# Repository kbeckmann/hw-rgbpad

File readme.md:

See [https://dox.xil.se/projects/rgbpad/](https://dox.xil.se/projects/rgbpad/)

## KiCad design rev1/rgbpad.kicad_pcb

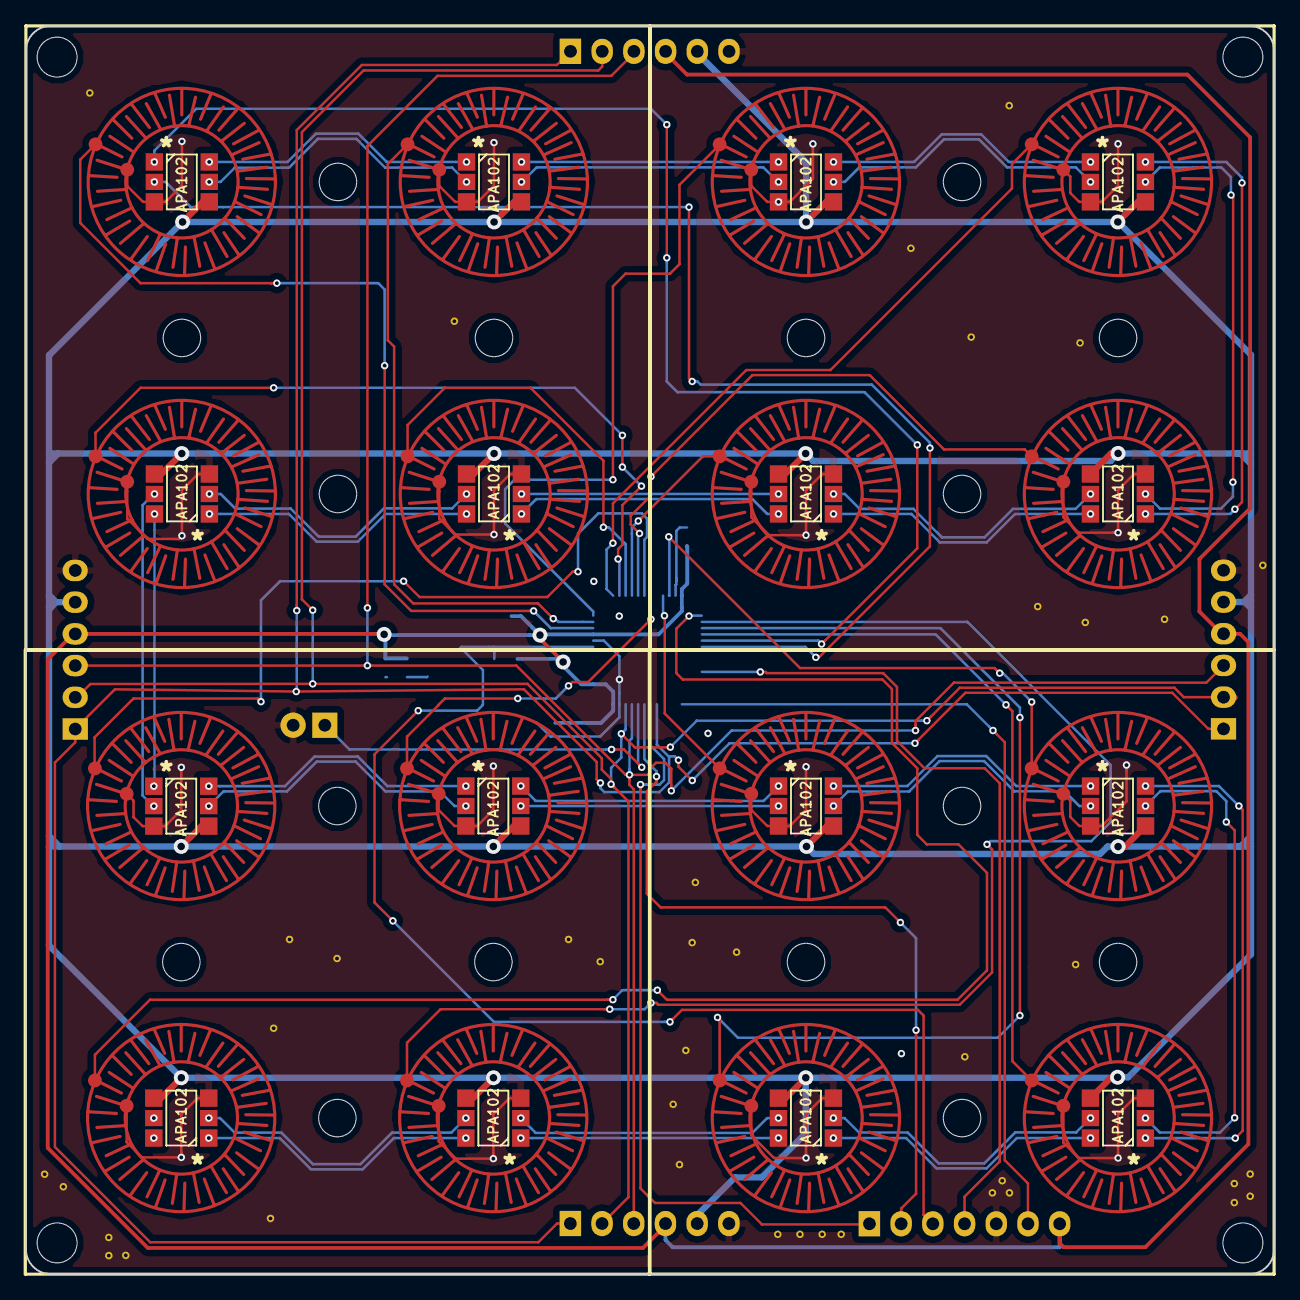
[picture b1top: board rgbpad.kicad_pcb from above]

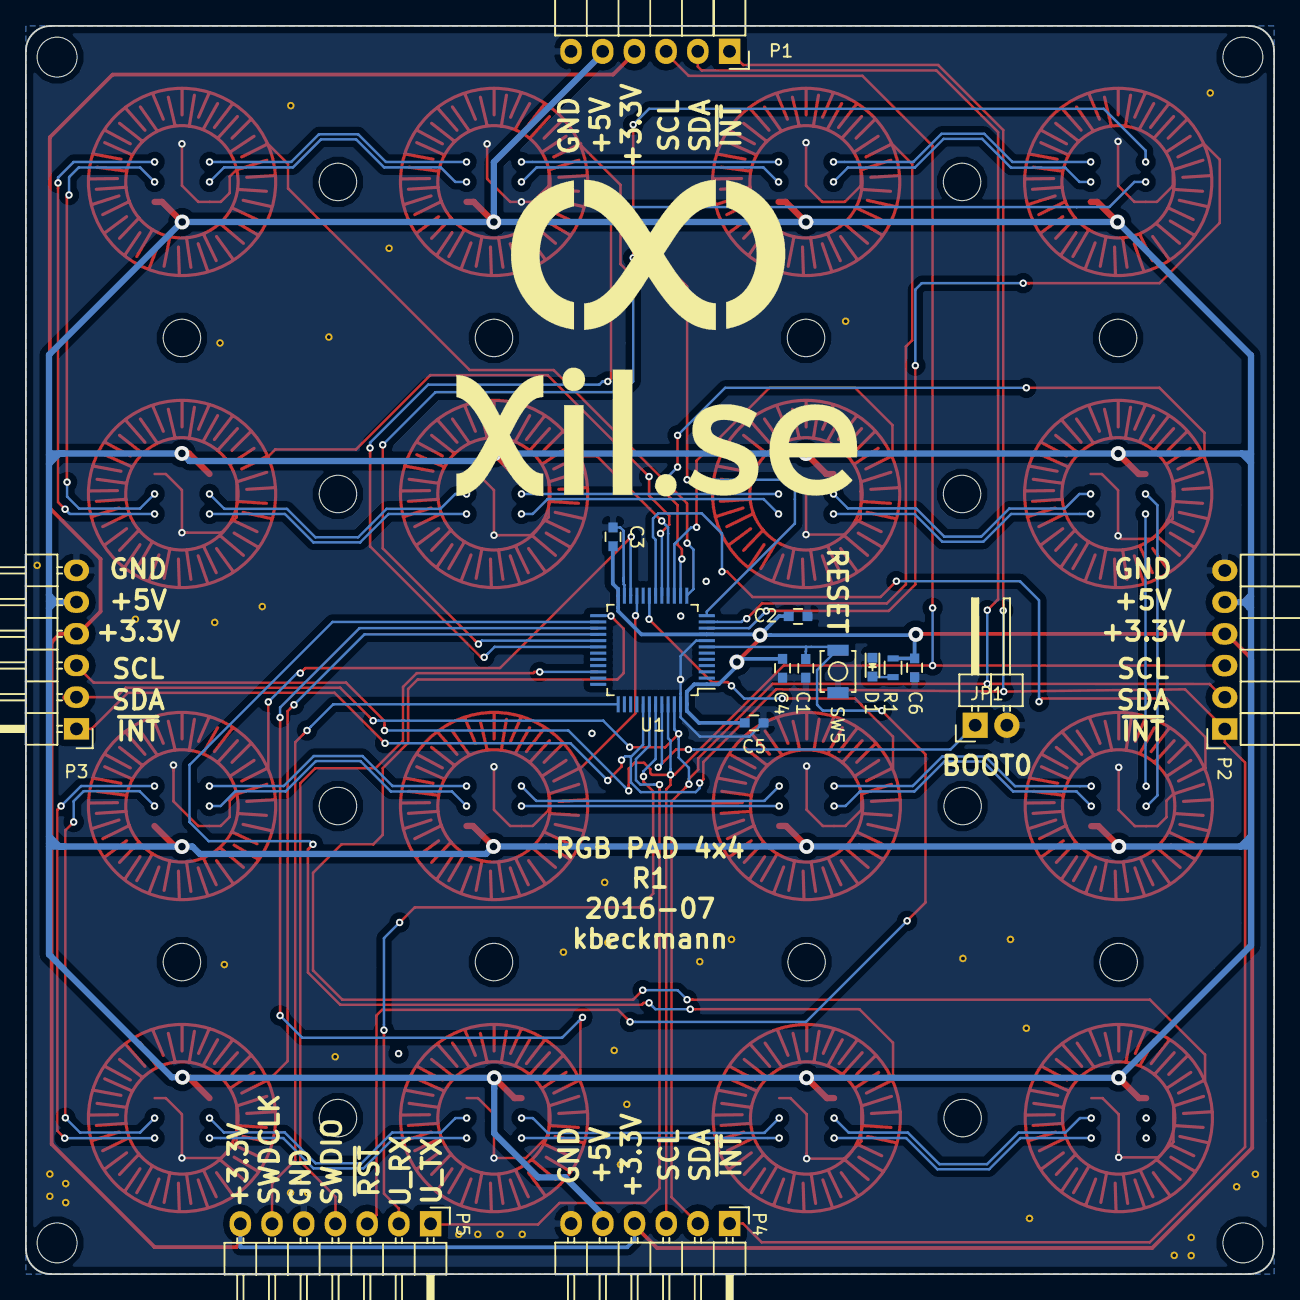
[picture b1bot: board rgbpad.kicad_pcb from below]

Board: 2 copper layers, 100.0 x 100.0 mm, 36 parts (16 on the bottom side), 61 nets.

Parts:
C1, C2, C3, C4, C5: 100n; C_0603
C6: 4u7; C_0603
D1: LED; LED_0603
JP1: JUMPER; Pin_Header_Angled_1x02
P1: CONN_01X06_TOP; Socket_Strip_Angled_1x06
P2: CONN_01X06_LEFT; Socket_Strip_Angled_1x06
P3: CONN_01X06_RIGHT; Pin_Header_Angled_1x06
P4: CONN_01X06_BOTTOM; Pin_Header_Angled_1x06
P5: CONN_01X07_DEBUG; Pin_Header_Angled_1x07
R1: 360; R_0603
SW1, SW2, SW3, SW4: SW_PUSH_2X2; BUTTONPAD-2X2
SW5: SW_PUSH_RST; SW_SPST_B3U-1000P
U1: STM32F030C8Tx; LQFP-48_7x7mm_Pitch0.5mm
U2, U3, U4, U5, U6, U7, U8, U9, U10, U11, U12, U13, U14, U15, U16, U17: APA102

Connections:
+3V3: C2.2, C3.2, C4.2, C5.2, C6.2, P1.4, P2.4, P3.4, P4.4, P5.7, R1.2, U1.1, U1.9, U1.24, U1.48
+5V: P1.5, P2.5, P3.5, P4.5, U2.4, U3.4, U4.4, U5.4, U6.4, U7.4, U8.4, U9.4, U10.4, U11.4, U12.4, U13.4, U14.4, U15.4, U16.4, U17.4
/4x4_LED/CIN: U1.30, U2.2
/4x4_LED/DIN: U1.29, U2.1
/STM32 controller/BOOT0: JP1.1, U1.44
/STM32 controller/BTN1: SW1.1, U1.10
/STM32 controller/BTN2: SW1.3, U1.11
/STM32 controller/BTN3: SW2.1, U1.12
/STM32 controller/BTN4: SW2.3, U1.13
/STM32 controller/BTN5: SW1.5, U1.14
/STM32 controller/BTN6: SW1.7, U1.15
/STM32 controller/BTN7: SW2.5, U1.16
/STM32 controller/BTN8: SW2.7, U1.17
/STM32 controller/BTN9: SW3.1, U1.18
/STM32 controller/BTN10: SW3.3, U1.19
/STM32 controller/BTN11: SW4.1, U1.21
/STM32 controller/BTN12: SW4.3, U1.22
/STM32 controller/BTN13: SW3.5, U1.25
/STM32 controller/BTN14: SW3.7, U1.26
/STM32 controller/BTN15: SW4.5, U1.27
/STM32 controller/BTN16: SW4.7, U1.28
/STM32 controller/I2C_SCL: P1.3, P2.3, P3.3, P4.3, U1.45
/STM32 controller/I2C_SDA: P1.2, P2.2, P3.2, P4.2, U1.46
/STM32 controller/NINT: P1.1, P2.1, P3.1, P4.1, U1.41
/STM32 controller/NRST: C1.2, P5.3, SW5.2, U1.7
/STM32 controller/SYS_SWDCLK: P5.6, U1.37
/STM32 controller/SYS_SWDIO: P5.4, U1.34
/STM32 controller/USART_RX: P5.2, U1.43
/STM32 controller/USART_TX: P5.1, U1.42
GND: C1.1, C2.1, C3.1, C4.1, C5.1, C6.1, D1.1, JP1.2, P1.6, P2.6, P3.6, P4.6, P5.5, SW1.2, SW1.4, SW1.6, SW1.8, SW2.2, SW2.4, SW2.6, SW2.8, SW3.2, SW3.4, SW3.6, SW3.8, SW4.2, SW4.4, SW4.6, SW4.8, SW5.1, U1.8, U1.23, U1.47, U2.3, U3.3, U4.3, U5.3, U6.3, U7.3, U8.3, U9.3, U10.3, U11.3, U12.3, U13.3, U14.3, U15.3, U16.3, U17.3
unnamed: D1.2, R1.1
unnamed: U2.5, U3.2
unnamed: U2.6, U3.1
unnamed: U3.5, U4.2
unnamed: U3.6, U4.1
unnamed: U4.5, U5.2
unnamed: U4.6, U5.1
unnamed: U5.5, U6.2
unnamed: U5.6, U6.1
unnamed: U6.5, U7.2
unnamed: U6.6, U7.1
unnamed: U7.5, U8.2
unnamed: U7.6, U8.1
unnamed: U8.5, U9.2
unnamed: U8.6, U9.1
unnamed: U9.6, U10.1
unnamed: U9.5, U10.2
unnamed: U10.5, U11.2
unnamed: U10.6, U11.1
unnamed: U11.5, U12.2
unnamed: U11.6, U12.1
unnamed: U12.5, U13.2
unnamed: U12.6, U13.1
unnamed: U13.5, U14.2
unnamed: U13.6, U14.1
unnamed: U14.5, U15.2
unnamed: U14.6, U15.1
unnamed: U15.5, U16.2
unnamed: U15.6, U16.1
unnamed: U16.5, U17.2
unnamed: U16.6, U17.1

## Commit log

2016-07-11 WIP. Closing in on rev1
2016-07-12 Schematic done. PCB left to do.
2016-07-12 This won't be easy. Or beautiful.
2016-07-13 Guess this is it..
2016-07-14 New PCB layout
2016-07-14 Minor fixes
2016-07-17 Final commit for R1
2016-07-20 Added solder mask...
2016-07-28 Added missing files
2016-08-05 add readme
